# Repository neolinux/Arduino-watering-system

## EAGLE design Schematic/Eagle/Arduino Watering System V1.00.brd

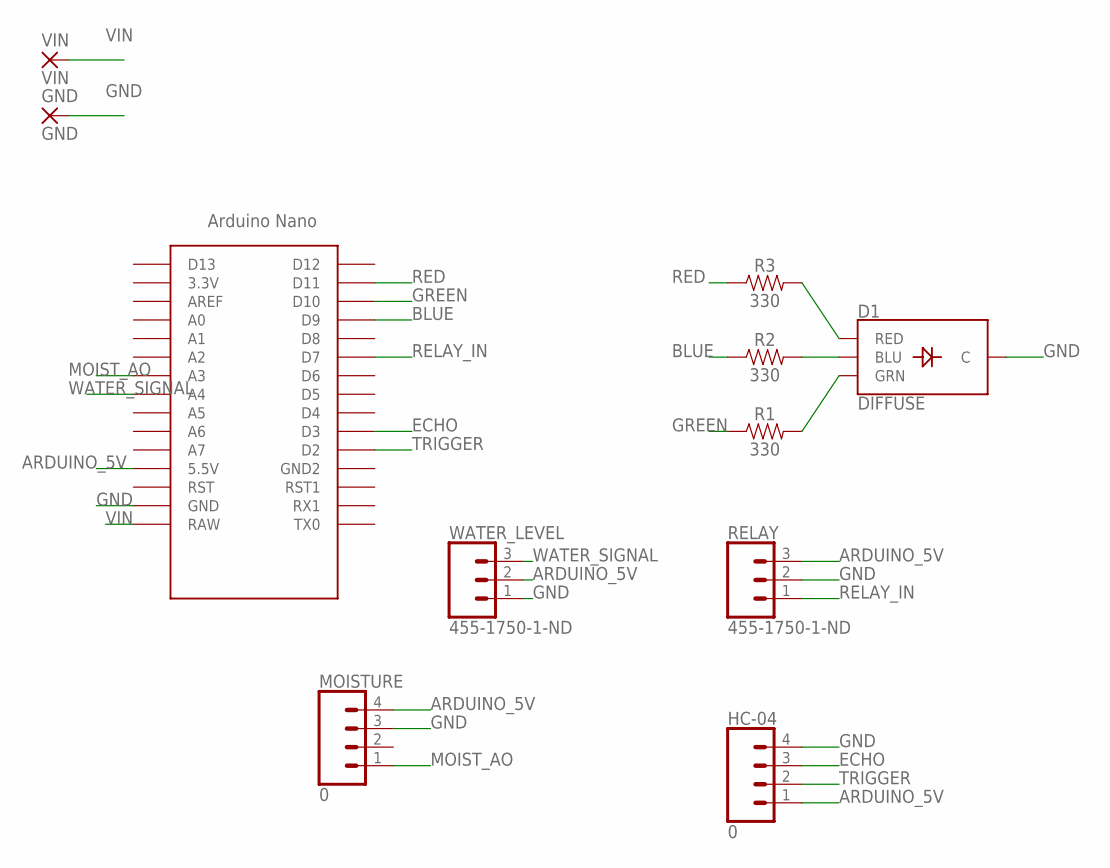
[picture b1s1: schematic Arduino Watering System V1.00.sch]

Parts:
D1: DIFFUSE; LED-RGB-THRU
GND: GND; SMD2,54-5,08
HC-04: 0; 1X04
MOISTURE: 0; 1X04
R1, R2, R3: 330; AXIAL-0.3
RELAY: 455-1750-1-ND; 1X03
U$1: NANO
VIN: VIN; SMD2,54-5,08
WATER_LEVEL: 455-1750-1-ND; 1X03

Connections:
ARDUINO_5V: HC-04.1, MOISTURE.4, RELAY.3, U$1.5V (5.5V), WATER_LEVEL.2
BLUE: R2.P$1 (1), U$1.D9
ECHO: HC-04.3, U$1.D3
GND: D1.2 (C), GND.1, HC-04.4, MOISTURE.3, RELAY.2, U$1.GND, WATER_LEVEL.1
GREEN: R1.P$1 (1), U$1.D10
MOIST_AO: MOISTURE.1, U$1.A3
unnamed: D1.3 (GRN), R1.P$2 (2)
unnamed: D1.4 (BLU), R2.P$2 (2)
unnamed: D1.1 (RED), R3.P$2 (2)
RED: R3.P$1 (1), U$1.D11
RELAY_IN: RELAY.1, U$1.D7
TRIGGER: HC-04.2, U$1.D2
VIN: U$1.RAW, VIN.1
WATER_SIGNAL: U$1.A4, WATER_LEVEL.3

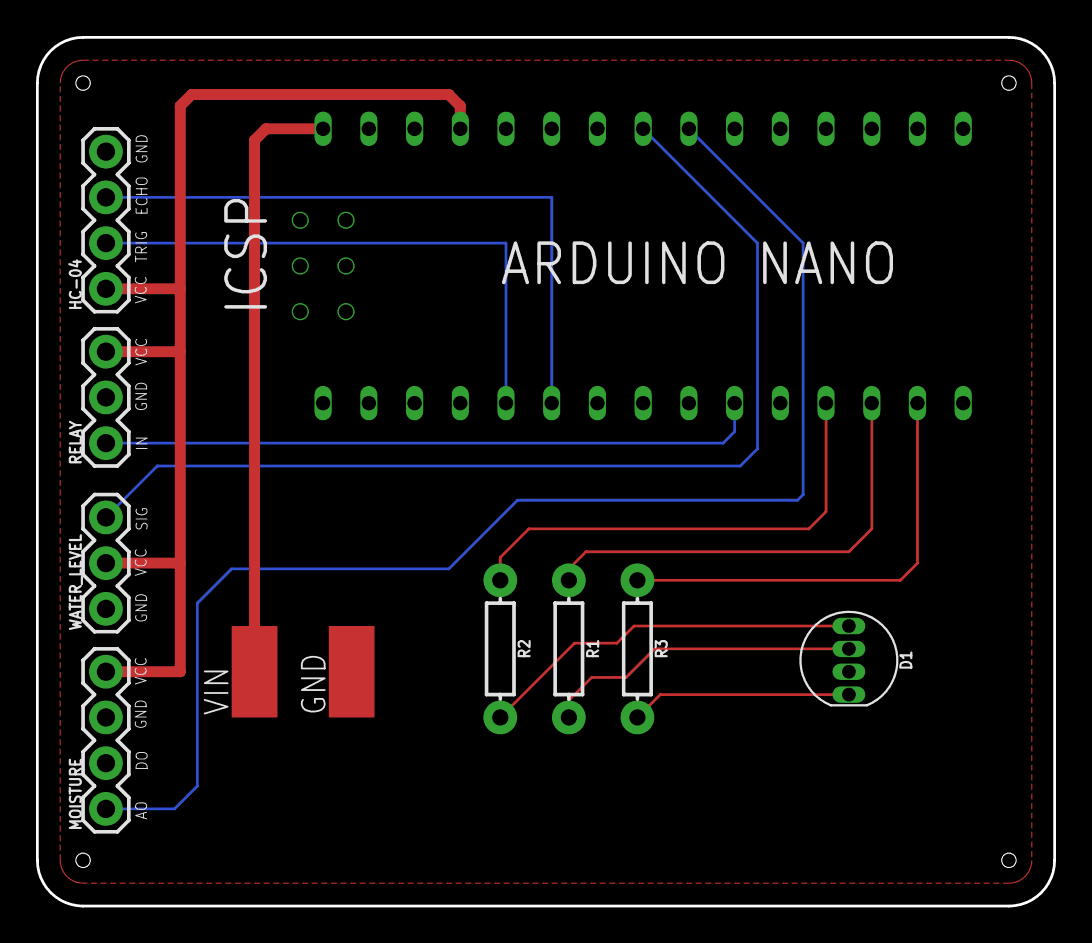
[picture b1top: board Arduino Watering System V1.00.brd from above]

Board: 2 copper layers, 56.5 x 48.3 mm, 11 parts (0 on the bottom side), 14 nets.

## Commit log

2018-03-09 Added Water distance sensor, changed the code and added more comments
2018-03-15 Update soil moisture Pin variable
2018-03-27 File Update and Schematic Upload

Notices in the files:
parts and their libraries:
SparkFun-LED: Licensing: Creative Commons ShareAlike 4.0 International - https://creativecommons.org/licenses/by-sa/4.0
m-pad-2.1: License : GNU General Public License version 2 (see bottom)
LICENSE: LGPL
